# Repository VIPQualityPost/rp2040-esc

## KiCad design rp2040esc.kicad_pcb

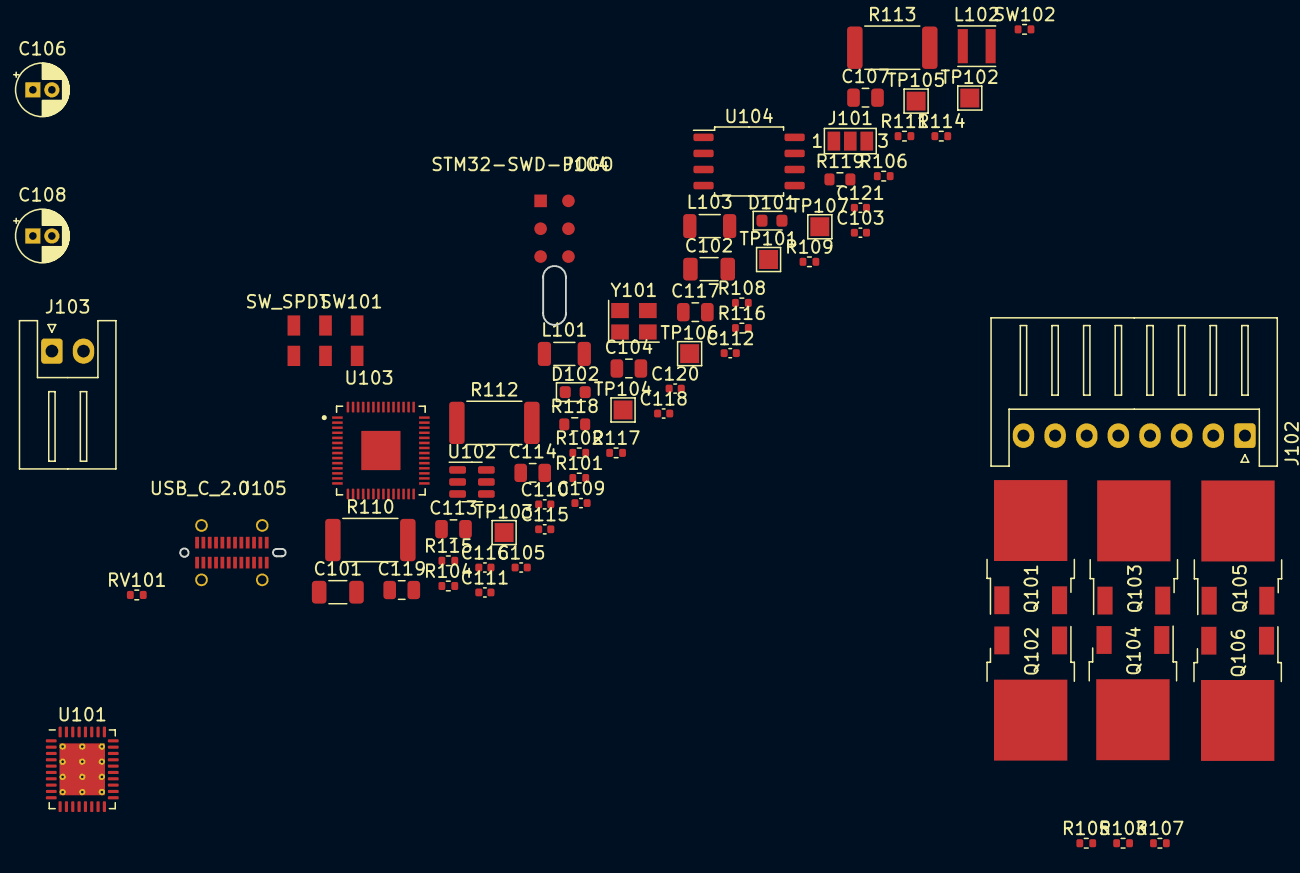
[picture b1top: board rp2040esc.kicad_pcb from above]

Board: 2 copper layers, 71 parts (0 on the bottom side), 57 nets, no tracks yet.

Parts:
C101, C102: 22uF; C_1206_3216Metric
C103, C109: 100nF; C_0402_1005Metric
C104: 4.7uF; C_0805_2012Metric
C105, C110, C112, C116: 470nF; C_0402_1005Metric
C106, C108: 100uF; CP_Radial_D4.0mm_P1.50mm
C107, C113, C114, C117, C119: 10uF; C_0805_2012Metric
C111, C115, C118: 10nF; C_0402_1005Metric
C120, C121: 20pF; C_0402_1005Metric
D101, D102: LED; D_0603_1608Metric
J101: DRVSEL; SolderJumper-3_P1.3mm_Open_Pad1.0x1.5mm_NumberLabels
J102: BLDC; JST_XH_S8B-XH-A_1x08_P2.50mm_Horizontal
J103: 24VIN; JST_XH_S2B-XH-A_1x02_P2.50mm_Horizontal
J104: STM32-SWD-POGO; SWD_pogo_landing
J105: USB_C_2.0; 918-418K2022Y40004
L101, L103: 20uH; L_1206_3216Metric
L102: 4.7uH; L_Taiyo-Yuden_NR-30xx
Q101, Q102, Q103, Q104, Q105, Q106: NCE6020AK; TO-252-2
R101, R108, R116: 10k; R_0402_1005Metric
R102, R103, R104, R105, R106, R107: 22; R_0402_1005Metric
R109: 27k; R_0402_1005Metric
R110, R112, R113: 150m; R_2512_6332Metric
R111: 3.9k; R_0402_1005Metric
R114, R115: 5.1k; R_0402_1005Metric
R117: 1k; R_0402_1005Metric
R118, R119: 27R; R_0603_1608Metric
RV101: 10k; R_0402_1005Metric
SW101: SW_SPDT; JS202011JCQN
SW102: BOOT_SEL; R_0402_1005Metric
TP101: ENCU; TestPoint_Pad_1.5x1.5mm
TP102: ENCV; TestPoint_Pad_1.5x1.5mm
TP103: ENCW; TestPoint_Pad_1.5x1.5mm
TP104: U; TestPoint_Pad_1.5x1.5mm
TP105: V; TestPoint_Pad_1.5x1.5mm
TP106: W; TestPoint_Pad_1.5x1.5mm
TP107: TestPoint; TestPoint_Pad_1.5x1.5mm
U101: TMC6140; QFN-36-1EP_5x6mm_P0.5mm_EP3.6x4.1mm_ThermalVias
U102: RY8310; SOT-23-6
U103: RP2040; QFN40P700X700X90-57N
U104: W25Q32JVSS; SOIC-8_5.23x5.23mm_P1.27mm
Y101: 12MHz; Crystal_SMD_3225-4Pin_3.2x2.5mm

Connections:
+3V3: C113.1, J101.1, J104.1, L102.2, R111.2, RV101.1, SW101.1 (A), U103.1 (IOVDD), U103.10 (IOVDD), U103.22 (IOVDD), U103.33 (IOVDD), U103.42 (IOVDD), U103.43 (ADC_AVDD), U103.44 (VREG_VIN), U103.48 (USB_VDD), U103.49 (IOVDD), U104.8 (VCC)
+5V: J102.1, J105.A4 (VBUS), J105.A9 (VBUS), J105.B4 (VBUS), J105.B9 (VBUS)
+24V: C105.1, C106.1, C107.1, C108.1, C111.1, C114.1, C115.1, C117.1, C118.1, C119.1, J103.1, Q101.1 (D), Q103.1 (D), Q105.1 (D), U102.4 (EN), U102.5 (VIN)
BLDC_U: C110.2, J102.6, Q101.3 (S), Q102.1 (D), TP104.1
BLDC_V: C112.2, J102.7, Q103.3 (S), Q104.1 (D), TP105.1
BLDC_W: C116.2, J102.8, Q105.3 (S), Q106.1 (D), TP106.1
DRV: J101.2, U103.30 (GPIO19)
ERR: D101.2 (A), U101.12 (DIAG), U103.32 (GPIO21)
EXT_IN: TP107.1, U103.18 (GPIO15)
GND: C101.1, C102.1, C103.2, C104.2, C105.2, C106.2, C107.2, C108.2, C111.2, C113.2, C114.2, C115.2, C117.2, C118.2, C119.2, C120.2, C121.2, J101.3, J102.5, J103.2, J104.5, J105.A1 (GND), J105.A12 (GND), J105.B1 (GND), J105.B12 (GND), J105.S1 (SHIELD), R101.1, R108.2, R110.2, R112.2, R113.2, R114.1, R115.1, R116.2, SW101.3 (C), SW102.2, U102.2 (GND), U103.19 (TESTEN), U103.57 (GND), U104.4 (GND), Y101.2, Y101.4
HALL_U: J102.2, TP101.1, U103.34 (GPIO22)
HALL_V: J102.3, TP102.1, U103.35 (GPIO23)
HALL_W: J102.4, TP103.1, U103.36 (GPIO24)
MANUAL: RV101.2, U103.41 (GPIO29/ADC3)
MANUAL_EN: SW101.2 (B), U103.37 (GPIO25)
unnamed: C101.2, C102.2, L103.1
unnamed: C109.1, U102.1 (BST)
unnamed: C109.2, L102.1, U102.6 (SW)
unnamed: D101.1 (K), R101.2
unnamed: D102.1 (K), R116.1
unnamed: D102.2 (A), U103.17 (GPIO14)
unnamed: J105.A5 (CC1), R114.2
unnamed: J105.B5 (CC2), R115.2
unnamed: L101.1, L103.2
unnamed: Q101.2 (G), R104.2
unnamed: Q102.2 (G), R105.2
unnamed: Q102.3 (S), R110.1
unnamed: Q103.2 (G), R103.2
unnamed: Q104.2 (G), R106.2
unnamed: Q104.3 (S), R112.1
unnamed: Q105.2 (G), R102.2
unnamed: Q106.2 (G), R107.2
unnamed: Q106.3 (S), R113.1
unnamed: R108.1, R109.1, U102.3 (FB)
unnamed: R109.2, R111.1
unnamed: R117.1, SW102.1
unnamed: R118.2, U103.46 (USB_DM)
unnamed: R119.2, U103.47 (USB_DP)
unnamed: U103.23 (DVDD), U103.45 (VREG_VOUT), U103.50 (DVDD)
QSPI_CS: R117.2, U103.56 (QSPI_CSN), U104.1 (~CS)
QSPI_D0: U103.53 (QSPI_SD0), U104.2 (DO(IO1))
QSPI_D1: U103.55 (QSPI_SD1), U104.5 (DI(IO0))
QSPI_D2: U103.54 (QSPI_SD2), U104.3 (IO2)
QSPI_D3: U103.51 (QSPI_SD3), U104.7 (IO3)
QSPI_SCLK: U103.52 (QSPI_SCLK), U104.6 (CLK)
RUN: J104.3, U103.26 (RUN)
SWCLK: J104.6, U103.24 (SWCLK)
SWD: J104.2, U103.25 (SWD)
UH: U101.3 (UH), U103.8 (GPIO6)
UL: U101.6 (UL), U103.6 (GPIO4)
USB_M: J105.A7 (D-), J105.B7 (D-), R118.1
USB_P: J105.A6 (D+), J105.B6 (D+), R119.1
VH: U101.4 (VH), U103.13 (GPIO10)
VL: U101.10 (VL), U103.11 (GPIO8)
WL: U101.7 (WL), U103.15 (GPIO12)
XIN: C120.1, U103.20 (XIN), Y101.1
XOUT: C121.1, U103.21 (XOUT), Y101.3

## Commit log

2022-11-18 initial files
2022-11-22 BOM and footprints
2022-11-30 work on layout
